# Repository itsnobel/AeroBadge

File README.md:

# AeroBadge - Cyberpunk Voice-Badge

A standalone, wearable(cz its tiny) cyberpunk voice-badge and off-grid walkie-talkie powered by ESP32-S3 and NRF24L01+. 
it fearures onboard Li-Po battery management, and an I2S audio subsystem for ultra-low latency peer-to-peer voice streaming(in a certain range of NRF24L01+) tha, audio logging, and offline smart commands without internet.

---

## Features
- Ultra-low latency voice streaming over NRF24L01+
- I2S Audio Subsystem (INMP441 Mic + MAX98357A Amp)
- small battery system that fits into the PCB.
- A camera that allows real time monitization.

---

## Components
- ESP23-3S Development board with camera
- NRF24L01+ Radio Module
- MAX98357A I2S Amplifier
- INMP441 Digital Microphone
- Battery

---

## Key Features

- ESP32-S3 Core - Powerful dual core MCU with built in DSP.
- I2S Audio System - Uses INMP441 MEMS mic for audio capture and MAX98357A class D DAC/amplifier for 8W audio.
- Off Grid - Uses NRF24L01+ 2.4Ghz radio for real time audio transmission.
- Wearable - Powered using external 3.7V Li-Po battery.

---

## Audio Pinout

* INMP441 Mic- SCK - GPIO7, WS - GPIO20, SD - GPIO3
* MAX98357A Amp - BCLK - GPIO7, LRC - GPIO20, DIN - GPIO1
* NRF24L01+: CE - GPIO9, CSN - GPIO10, SCK - GPIO12, MOSI - GPIO11, MISO - GPIO13

---

## Project Photos & Schematic
- Fully Designed by me. The PCB holds the ESP32-3S module. The dimension  of ESP32 mainboard and the PCB size is most likely the same. It is build in a compact area to make it as mobile as possible.
- The schematic of The main board-
- 
The PCB design-

The 2D view-

The 3D view-

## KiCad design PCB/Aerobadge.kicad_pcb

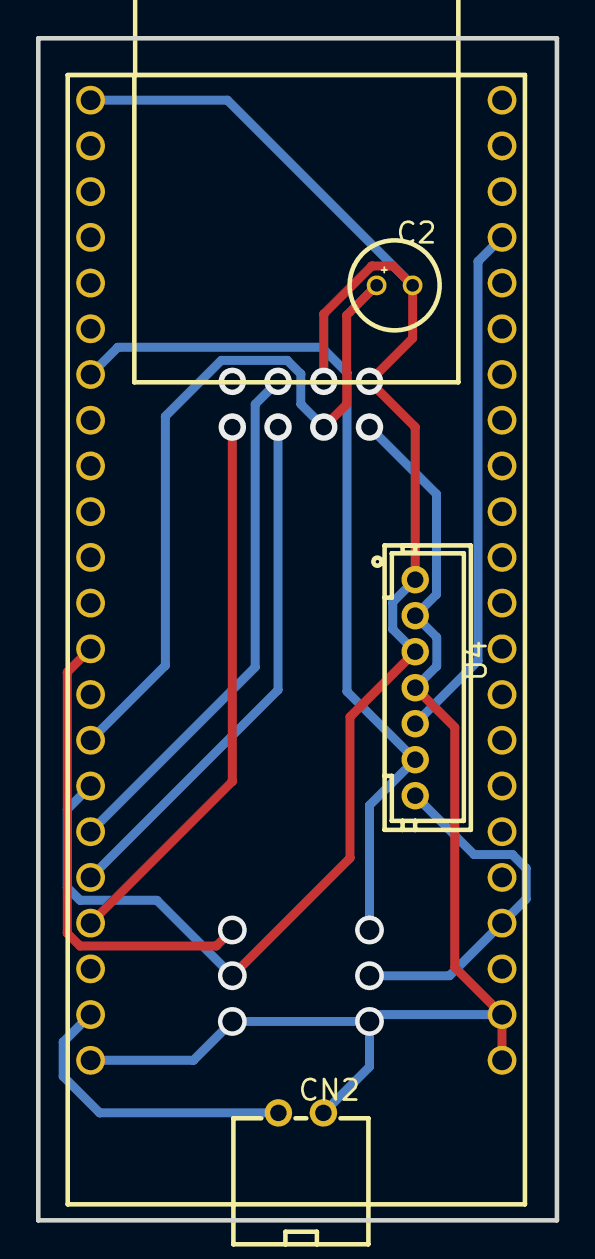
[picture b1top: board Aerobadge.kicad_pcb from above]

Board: 2 copper layers, 28.8 x 65.7 mm, 4 parts (0 on the bottom side), 7 nets.

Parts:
C2: 10uF; CAP-TH_BD5.0-P2.00-D0.5-FD_RYHG35V10UF
CN2: 2.54-2P WZDK-R PITCH CONNECTOR; CONN-TH_2.54-2P-WZDK-R-PITCH-CONNECTOR
U1: ESP32-S2-DEVKITC-1; COMM-TH_44P-L62.7-W25.4-P2.54-LS22.86-TL_ESP32-S2-DEVKITC-1
U4: HDR-1X7_C9900094784; CONN-TH_HDR-1X7

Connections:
U1_1: C2.2, U1.1, U1.16, U4.1, U4.3
U1_7: U1.7, U4.6
U1_15: C2.1, U1.15
U1_21: CN2.1, U1.21
U1_22: CN2.2, U1.22, U1.23, U1.24, U4.2, U4.4
U1_26: U1.26, U4.7
U1_41: U1.41, U4.5
